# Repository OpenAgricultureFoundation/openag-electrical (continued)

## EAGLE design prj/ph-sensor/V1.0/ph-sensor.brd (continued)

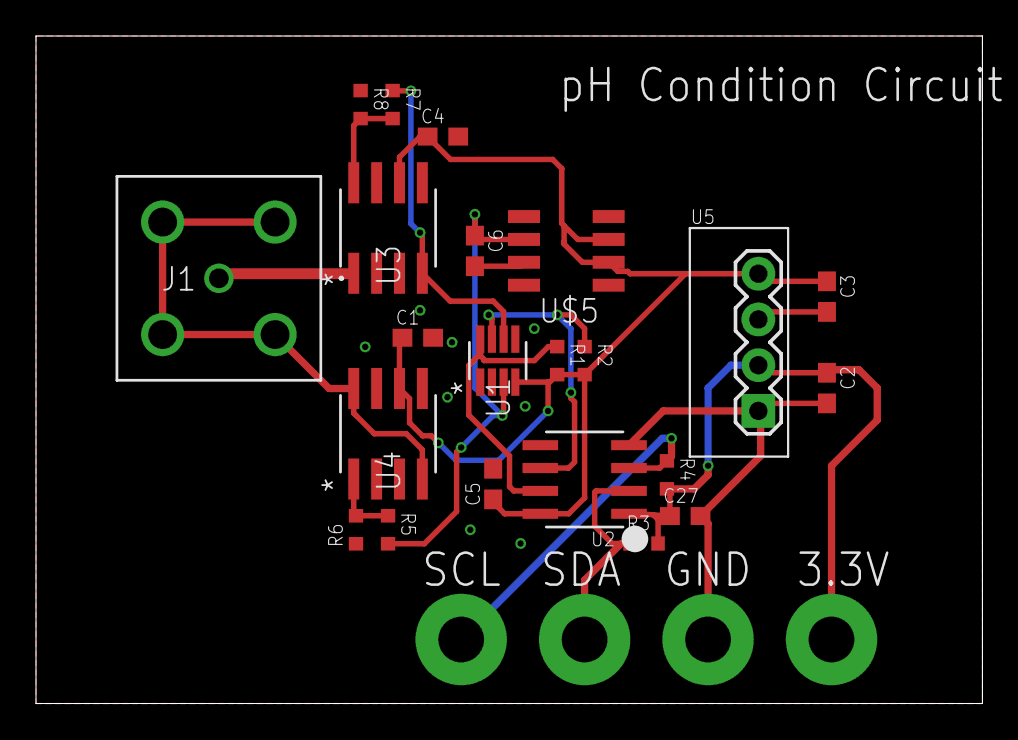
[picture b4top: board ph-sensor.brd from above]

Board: 2 copper layers, 52.6 x 37.1 mm, 22 parts (0 on the bottom side), 14 nets.
